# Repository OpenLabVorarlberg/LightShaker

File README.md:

# LightShaker
The LightShaker is a handheld PersistenceOfVision-Display featuring an STM32F0 controller, USB connectivity, 16 RGB LEDs and a 3-axis accelerometer
The Component selection is a tradeoff between easy assembly and price & availablility. The accelerometer is the only component that can't be soldered by hand. It could be omitted, but honestly, that's the coolest feature of it :)

The Lightshaker was designed for electronics events and classes with kids. With a bit of supervision (and the accelerometer preassembled), even beginners can build a really cool gadget. With the provided OpenSource Firmware a fully featured active and even per USB configurable POV display is the first cool Application of the LightShaker. 
But with the RGB-LEDs, USB-connectivity and the accelerometer, lots of other cool things are possible! For Example:
- Joystick, Mouse or customized analog Input device for the PC
- electronic level
- propeller clock
- ...

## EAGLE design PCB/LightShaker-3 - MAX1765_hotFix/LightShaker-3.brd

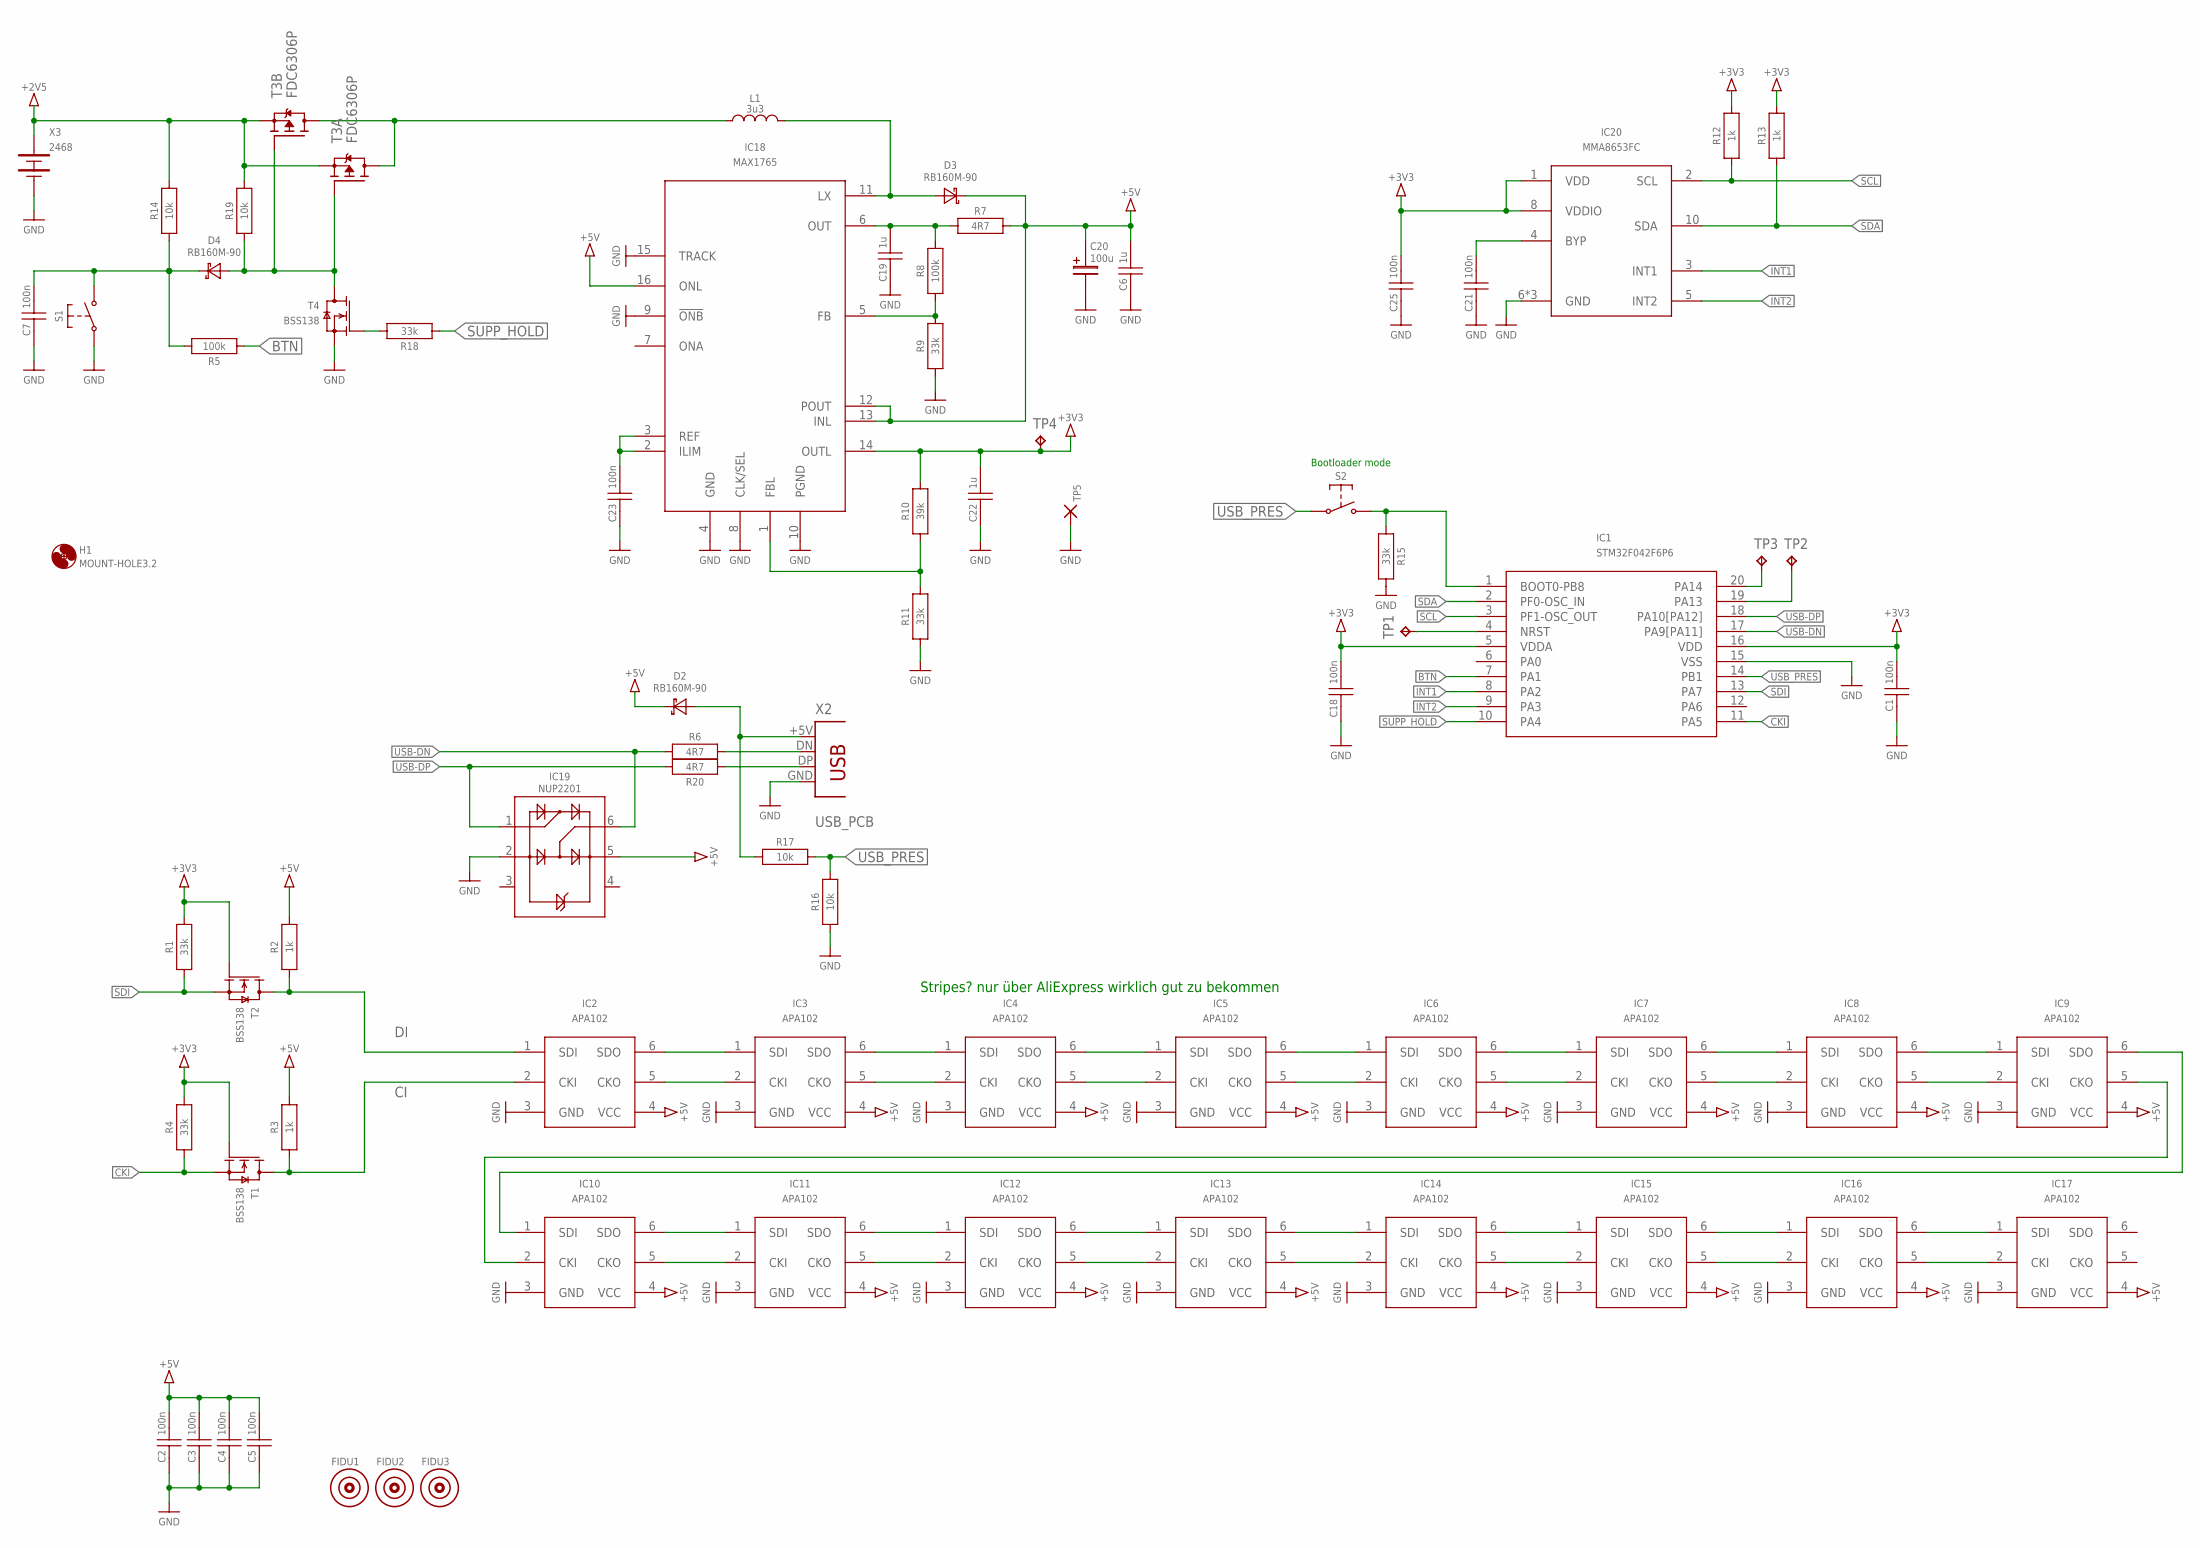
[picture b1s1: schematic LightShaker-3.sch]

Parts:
C1, C2, C3, C4, C5, C7, C18, C21, C23, C25: 100n; SM_1206; PARTNR E0001400
C6, C19, C22: 1u; SM_1206; PARTNR E0487200
C20: 100u; SM_SIZE-D; PARTNR E0242200
D2, D3, D4: RB160M-90; SM_SOD123_POL
FIDU1, FIDU2, FIDU3: FIDU_ROUND_NEW; FIDUCIAL_LOETSTOPP
H1: MOUNT-HOLE3.2; 3.2
IC1: STM32F042F6P6; SM_TSSOP20; PARTNR P1480012
IC2, IC3, IC4, IC5, IC6, IC7, IC8, IC9, IC10, IC11, IC12, IC13, IC14, IC15, IC16, IC17: APA102; SM_LED_PLCC6
IC18: MAX1765; SM_QSOP16; PARTNR P1480011
IC19: NUP2201; TSOP6
IC20: MMA8653FC; SM_DFN10; PARTNR P1480013
L1: 3u3; SM_L_MOS6020; PARTNR E0517800
R1, R4, R9, R11, R15, R18: 33k; SM_1206; PARTNR E0149800
R2, R3, R12, R13: 1k; SM_1206; PARTNR E0002500
R5: 100k; SM_1206
R6, R20: 4R7; SM_1206
R7: 4R7; SM_1206; PARTNR E0821300
R8: 100k; SM_1206; PARTNR E0002800
R10: 39k; SM_1206
R14, R16, R17: 10k; SM_1206; PARTNR E0002700
R19: 10k; SM_1206; PARTNR E0002800
S1, S2: PUSH-BUTTON_SMD
T1, T2, T4: BSS138; SM_SOT23
T3: FDC6306P; TSOP6; PARTNR E0662100
TP1, TP2, TP3, TP4: TPTP12R; TP12R
TP5: CHECKER_1206; SM_RCW_1206
X2: USB_PCB
X3: 2468

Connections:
+2V5: R14.2, R19.2, T3.2 (S), T3.5 (S), X3.POS
+3V3: C1.2, C18.2, C22.2, C25.2, IC1.5 (VDDA), IC1.16 (VDD), IC18.14 (OUTL), IC20.1 (VDD), IC20.8 (VDDIO), R1.2, R4.2, R10.2, R12.2, R13.2, T1.1 (G), T2.1 (G), TP4.TP
+5V: C2.2, C3.2, C4.2, C5.2, C6.2, C20.POS, D2.C, D3.C, IC2.4 (VCC), IC3.4 (VCC), IC4.4 (VCC), IC5.4 (VCC), IC6.4 (VCC), IC7.4 (VCC), IC8.4 (VCC), IC9.4 (VCC), IC10.4 (VCC), IC11.4 (VCC), IC12.4 (VCC), IC13.4 (VCC), IC14.4 (VCC), IC15.4 (VCC), IC16.4 (VCC), IC17.4 (VCC), IC18.12 (POUT), IC18.13 (INL), IC18.16 (ONL), IC19.5 (VP), R2.2, R3.2, R7.2
BTN: IC1.7 (PA1), R5.1
BTN1: C7.2, D4.C, R5.2, R14.1, S1.3 (S), S1.4 (S)
CI: IC2.2 (CKI), R3.1, T1.3 (D)
CKI: IC1.11 (PA5), R4.1, T1.2 (S)
DI: IC2.1 (SDI), R2.1, T2.3 (D)
GATE: D4.A, R19.1, T3.1 (G), T3.3 (G), T4.3 (D)
GND: C1.1, C2.1, C3.1, C4.1, C5.1, C6.1, C7.1, C18.1, C19.1, C20.NEG, C21.1, C22.1, C23.1, C25.1, IC1.15 (VSS), IC2.3 (GND), IC3.3 (GND), IC4.3 (GND), IC5.3 (GND), IC6.3 (GND), IC7.3 (GND), IC8.3 (GND), IC9.3 (GND), IC10.3 (GND), IC11.3 (GND), IC12.3 (GND), IC13.3 (GND), IC14.3 (GND), IC15.3 (GND), IC16.3 (GND), IC17.3 (GND), IC18.4 (GND), IC18.8 (CLK/SEL), IC18.9 (!ONB), IC18.10 (PGND), IC18.15 (TRACK), IC19.2 (GND), IC20.6 (GND), IC20.7 (GND), IC20.9 (GND), R9.1, R11.1, R15.2, R16.1, S1.1, S1.2, T4.2 (S), TP5.1, X2.GND, X3.NEG
INT1: IC1.8 (PA2), IC20.3 (INT1)
INT2: IC1.9 (PA3), IC20.5 (INT2)
unnamed: IC2.6 (SDO), IC3.1 (SDI)
unnamed: IC2.5 (CKO), IC3.2 (CKI)
unnamed: R18.2, T4.1 (G)
unnamed: IC3.6 (SDO), IC4.1 (SDI)
unnamed: IC3.5 (CKO), IC4.2 (CKI)
unnamed: R20.1, X2.DP
unnamed: IC4.6 (SDO), IC5.1 (SDI)
unnamed: IC4.5 (CKO), IC5.2 (CKI)
unnamed: R6.2, X2.DN
unnamed: IC6.6 (SDO), IC7.1 (SDI)
unnamed: IC6.5 (CKO), IC7.2 (CKI)
unnamed: IC7.6 (SDO), IC8.1 (SDI)
unnamed: IC7.5 (CKO), IC8.2 (CKI)
unnamed: L1.1, T3.4 (D), T3.6 (D)
unnamed: IC8.6 (SDO), IC9.1 (SDI)
unnamed: IC8.5 (CKO), IC9.2 (CKI)
unnamed: IC1.4 (NRST), TP1.TP
unnamed: IC10.6 (SDO), IC11.1 (SDI)
unnamed: IC10.5 (CKO), IC11.2 (CKI)
unnamed: IC1.1 (BOOT0-PB8), R15.1, S2.3 (S), S2.4 (S)
unnamed: IC11.6 (SDO), IC12.1 (SDI)
unnamed: IC11.5 (CKO), IC12.2 (CKI)
unnamed: IC1.20 (PA14), TP3.TP
unnamed: IC12.6 (SDO), IC13.1 (SDI)
unnamed: IC12.5 (CKO), IC13.2 (CKI)
unnamed: IC1.19 (PA13), TP2.TP
unnamed: IC14.6 (SDO), IC15.1 (SDI)
unnamed: IC14.5 (CKO), IC15.2 (CKI)
unnamed: IC15.6 (SDO), IC16.1 (SDI)
unnamed: IC15.5 (CKO), IC16.2 (CKI)
unnamed: C19.2, IC18.6 (OUT), R7.1, R8.2
unnamed: IC16.6 (SDO), IC17.1 (SDI)
unnamed: IC16.5 (CKO), IC17.2 (CKI)
unnamed: IC18.5 (FB), R8.1, R9.2
unnamed: D3.A, IC18.11 (LX), L1.2
unnamed: IC5.5 (CKO), IC6.2 (CKI)
unnamed: IC5.6 (SDO), IC6.1 (SDI)
unnamed: IC18.1 (FBL), R10.1, R11.2
unnamed: IC9.5 (CKO), IC10.2 (CKI)
unnamed: IC9.6 (SDO), IC10.1 (SDI)
unnamed: IC13.5 (CKO), IC14.2 (CKI)
unnamed: IC13.6 (SDO), IC14.1 (SDI)
unnamed: C21.2, IC20.4 (BYP)
unnamed: C23.2, IC18.2 (ILIM), IC18.3 (REF)
SCL: IC1.3 (PF1-OSC_OUT), IC20.2 (SCL), R12.1
SDA: IC1.2 (PF0-OSC_IN), IC20.10 (SDA), R13.1
SDI: IC1.13 (PA7), R1.1, T2.2 (S)
SUPP_HOLD: IC1.10 (PA4), R18.1
USB-DN: IC1.17 (PA9[PA11]), IC19.6 (IO2), R6.1
USB-DP: IC1.18 (PA10[PA12]), IC19.1 (IO1), R20.2
USB_PRES: IC1.14 (PB1), R16.2, R17.2, S2.1, S2.2
VUSB: D2.A, R17.1, X2.+5V

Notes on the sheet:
Bootloader mode
Stripes? nur über AliExpress wirklich gut zu bekommen

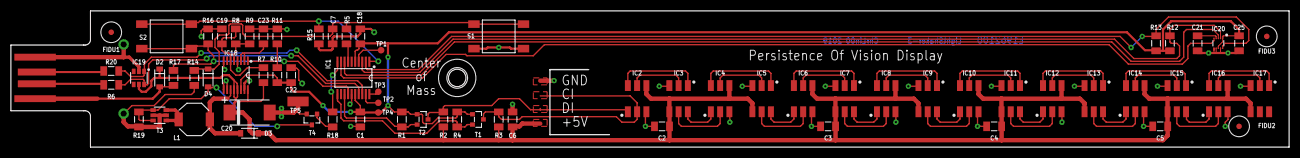
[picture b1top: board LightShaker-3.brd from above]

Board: 2 copper layers, 234.6 x 25.0 mm, 76 parts (1 on the bottom side), 64 nets.

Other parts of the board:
U$2: DOCFIELD

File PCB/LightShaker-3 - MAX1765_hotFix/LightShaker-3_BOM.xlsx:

LightShaker-3 |  |  | Pieces | 64
 | Qty | Value | Device | Package | Parts | Description
 | 2 |  | PUSH-BUTTON_SMD | PUSH-BUTTON_SMD | S1, S2 | Push Button Switch
 | 2 | 100k | R1206 | SM_1206 | R5, R8 | Resistor
 | 10 | 100n | C1206 | SM_1206 | C1, C2, C3, C4, C5, C7, C18, C21, C23, C25 | Capacitor
 | 1 | 100u | CPOLSIZE-D | SM_SIZE-D | C20 | Capacitor
 | 4 | 10k | R1206 | SM_1206 | R14, R16, R17, R19 | Resistor
 | 4 | 1k | R1206 | SM_1206 | R2, R3, R12, R13 | Resistor
 | 3 | 1u | C1206 | SM_1206 | C6, C19, C22 | Capacitor
 | 1 | 2468 | 2468 | 2468 | X3 | Batteryholder
 | 6 | 33k | R1206 | SM_1206 | R1, R4, R9, R10, R11, R15, R18 | Resistor
 | 1 | 3u3 | L_MOS6020 | SM_L_MOS6020 | L1 | Inductor
 | 3 | 4R7 | R1206 | SM_1206 | R6, R7, R20 | Resistor
 | 16 | SK9822 | SK9822 | SM_LED_PLCC6 | IC2, IC3, IC4, IC5, IC6, IC7, IC8, IC9, IC10 IC11, IC12, IC13, IC14, IC15, IC16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 | SMD LED
 | 3 | BSS138 | BSS138 | SM_SOT23 | T1, T2, T4 | BSS138 NMOSFET SOT23
 | 1 | FDC6306P | FDC6306P | TSOP6 | T3
 | 1 | MAX1765 | MAX1765 | SM_QSOP16 | IC18
 | 1 | MMA8653FC | MMA8653FC | SM_DFN10 | IC20
 | 1 | NUP2201 | NUP2201 | TSOP6 | IC19 | ESD Protection
 | 3 | RB160M-90 | RB160M-90 | SM_SOD123_POL | D2, D3, D4 | Diode RB160M-90
 | 1 | STM32F042F6P6 | STM32F042F6P6 | SM_TSSOP20 | IC1
 | Additional component
 | 1 | increas the PCB-USB connector thickness by using 4 layers of 3M467MP adhesive p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 |  |  |  | 58um transparent foil

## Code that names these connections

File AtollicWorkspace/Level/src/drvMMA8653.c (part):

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
	//gpio init
	GPIO_InitTypeDef GPIO_InitStruct;
	//configure PINs PF0 and PF1 as AF OD out
	GPIO_InitStruct.GPIO_Pin = GPIO_Pin_0 | GPIO_Pin_1;
	GPIO_InitStruct.GPIO_Mode = GPIO_Mode_AF;
	GPIO_InitStruct.GPIO_OType = GPIO_OType_OD;
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	GPIO_PinAFConfig(GPIOF,GPIO_PinSource0,GPIO_AF_1);
	GPIO_PinAFConfig(GPIOF,GPIO_PinSource1,GPIO_AF_1);

	//configure PINs PA2 and PA3 as inputs for the interrupt lines
	GPIO_InitStruct.GPIO_Pin = GPIO_Pin_2 | GPIO_Pin_3;
	GPIO_InitStruct.GPIO_Mode = GPIO_Mode_IN;
	GPIO_InitStruct.GPIO_PuPd = GPIO_PuPd_UP;
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	I2C_BitHandling(REG_CTRL_REG_5,1<<0,Bit_SET);

	//set up the Interrupt in the STM32!
	//INT1 is connected to PA2 -> EXTI2 line
	//enable the clock for the syscfg module
	RCC_APB2PeriphClockCmd(RCC_APB2Periph_SYSCFG, ENABLE);
	//enable PA2 interrupt source
	SYSCFG_EXTILineConfig(EXTI_PortSourceGPIOA, EXTI_PinSource2);
	//configure and enable the exti2 line
	EXTI_InitTypeDef EXTI_InitStruct;
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
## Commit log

2016-09-23 initial commit of the complete workspace
2016-09-26 reorganized Workspace:
2016-09-26 reorganized workspace: new shared proects containing libraries and drivers, all other projects reference this - seismograph has strange build errors
2016-10-03 bugfix in Level.main.c -> level works now added playground (framework-like project)
2016-10-19 Fixed project references and added .gitignore files
    Relative project reference paths are used instead of absolute ones
2019-07-30 added Docu, Tools and PCB for POVDisplay-2
2019-07-30 added PCB-Data for LightShaker-3
2019-10-16 updated FW for work with Lightshaker-3 HW by adding drvPower to all projects, didn't fix all existing Bugs
2019-10-17 cleaned up BOM
2019-10-21 reworked drvApa102 to bare-metal
2019-10-22 replaced the eeprom emulator with a custom lightweight Non-Volatile memory management
2019-10-22 finished debugging of POV_Display project for Lightshaker-3 -> works now. Added project to test a new usb implementation
2019-10-23 Level_FW: moved LED-Test in front of I2C-init to make debugging easier
2019-10-23 POV_display: if color is configured to 0,0,0, set it to 255,255,255 at init; added released_firmware folder
2019-10-23 added Manual removed old stuff not fitting to the LightShaker-3 any more
2019-10-25 included patch from robin -> Playground has some nice high-level framework functions with descriptions
2019-10-28 added external tool and run config for DFU_Bootloader
2019-10-28 bugfix in external tool config
2019-10-29 bugfix in drvDisplay_init: Rows_visible was out of bounds built dfu-file of POV_Display
2019-10-30 another bugfix in the display_init of POV_Display including dfu file of fixed FW; made Playground a bit easier to use
2021-09-06 added all the changes done by Adrian and Stefan
2021-09-15 imported the project to newest Cube ide
2021-10-06 reporked appSwitching and init, new button debouncing in drv_Power, everything prepared for integration of playground, povDisplay and Level running as Apps
2021-10-06 integrated Playground into app-selection, lots of refactoring, POV-Display, Level and Playground working
2021-10-07 added new app 'ColorPicker' and HSV to RGB conversion, changed order of apps
2021-10-07 small changes in the behavior of the power_hold feature: no power hold when powered by usb, every button press sets the hold-timer to 10s
2021-10-07 added double-click to button handler, reworked button-hold handling, colorPicker can save color to NvMemory for the POV-Display
2021-10-08 added method in neopixels-driver to activate the color savced in nvmemory
2021-10-08 optimized flash usage by directly allocating picture data in special flash section (drvNvMemory.c)
2021-10-14 commit of the last leftover fw changes
2021-10-14 release of Multi-FW V1.0
2021-10-14 updated schematic pdf and bom
2021-10-14 updated manual
2021-10-25 some commenting and refactoring in Playground, no changes to functionality
2021-10-28 add Neopixels_UpdateColor to enable multi-color patterns
2021-10-28 add some methods for more granular LED control
2021-10-28 improve method
